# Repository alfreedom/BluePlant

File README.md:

# BluePlant
Dispositivo de sensado para plantas ornamentales y jardines

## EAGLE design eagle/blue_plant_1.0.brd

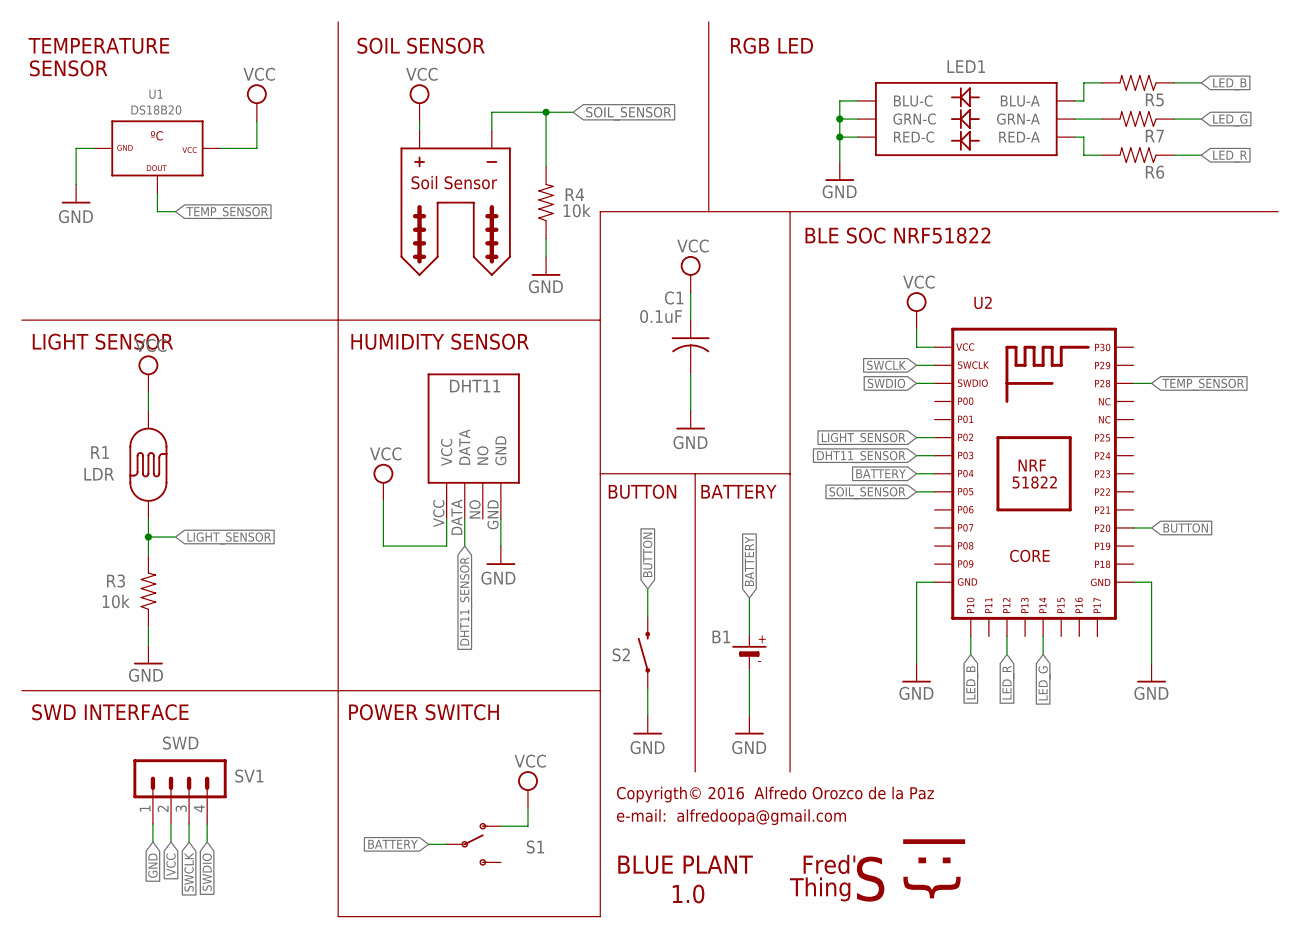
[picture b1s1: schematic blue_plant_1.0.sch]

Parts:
B1: BATTERYCR2032; CR2032
C1: 0.1uF; C025_050-025X075
LED1: RGB-5050; LED-TRICOLOR-5050
R1: LDR; PHOTOCELL-KIT
R2: SOIL-SENSOR; SOIL-SENSOR-1
R3, R4: 10k; AXIAL-0.3-KIT
R5, R6, R7: RESISTORKIT; AXIAL-0.3-KIT
S1: SWITCH-SPDT-SMD-A; SWITCH-SPST-SMD-A
S2: SWITCH-MOMENTARY-2SMD; TACTILE_SWITCH_SMD
SV1: SWD; MA04-1
U1: DS18B20; TO-92
U2: NRF51822-CORE-2; NRF51822-CORE2
U$1: DHT11

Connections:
BATTERY: B1.+, S1.2, U2.P18 (P04)
BUTTON: S2.3 (2), U2.P20
DHT11_SENSOR: U2.P17 (P03), U$1.DATA
GND: B1.-, C1.2, LED1.4 (BLU-C), LED1.5 (RED-C), LED1.6 (GRN-C), R3.P$1 (1), R4.P$1 (1), S2.1, SV1.1, U1.1 (GND), U2.P1 (GND1), U2.P12 (GND2), U$1.GND
LED_B: R5.P$1 (1), U2.P32 (P10)
LED_G: R7.P$1 (1), U2.P28 (P14)
LED_R: R6.P$1 (1), U2.P30 (P12)
LIGHT_SENSOR: R1.1, R3.P$2 (2), U2.P16 (P02)
unnamed: LED1.1 (GRN-A), R7.P$2 (2)
unnamed: LED1.3 (BLU-A), R5.P$2 (2)
unnamed: LED1.2 (RED-A), R6.P$2 (2)
SOIL_SENSOR: R2.P$1 (PG), R4.P$2 (2), U2.P35 (P05)
SWCLK: SV1.3, U2.P24 (SWDCLK)
SWDIO: SV1.4, U2.P23 (SWDIO)
TEMP_SENSOR: U1.2 (DOUT), U2.P9 (P28)
VCC: C1.1, R1.2, R2.P$2 (PS), S1.1 (O), SV1.2, U1.3 (VCC), U2.P11 (VCC), U$1.VCC

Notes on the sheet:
Copyrigth© 2016 Alfredo Orozco de la Paz
e-mail: alfredoopa@gmail.com
Fred'
{:|
BLUE PLANT
Thing
1.0
TEMPERATURE
SENSOR
SOIL SENSOR
RGB LED
BLE SOC NRF51822
POWER SWITCH
SWD INTERFACE
HUMIDITY SENSOR
LIGHT SENSOR
BUTTON
BATTERY

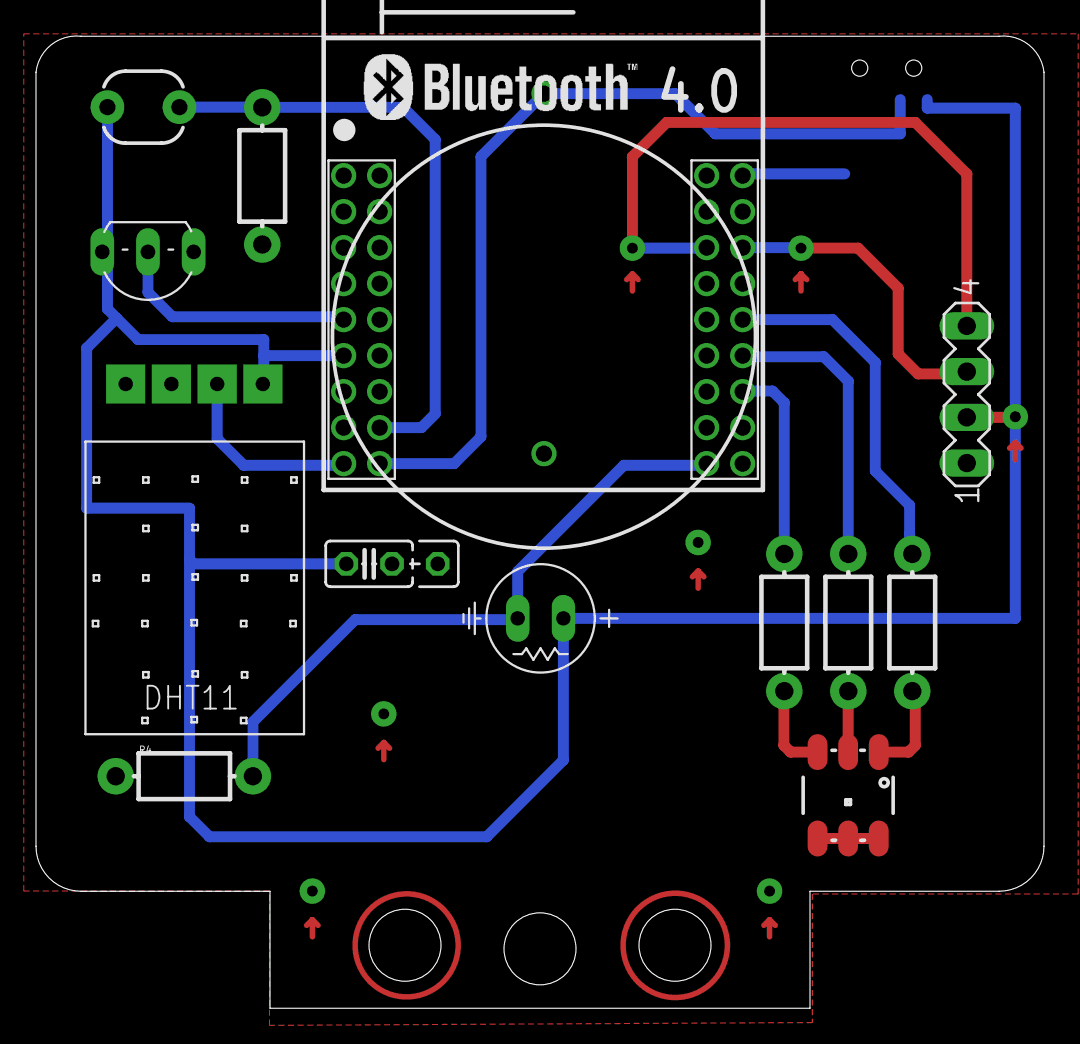
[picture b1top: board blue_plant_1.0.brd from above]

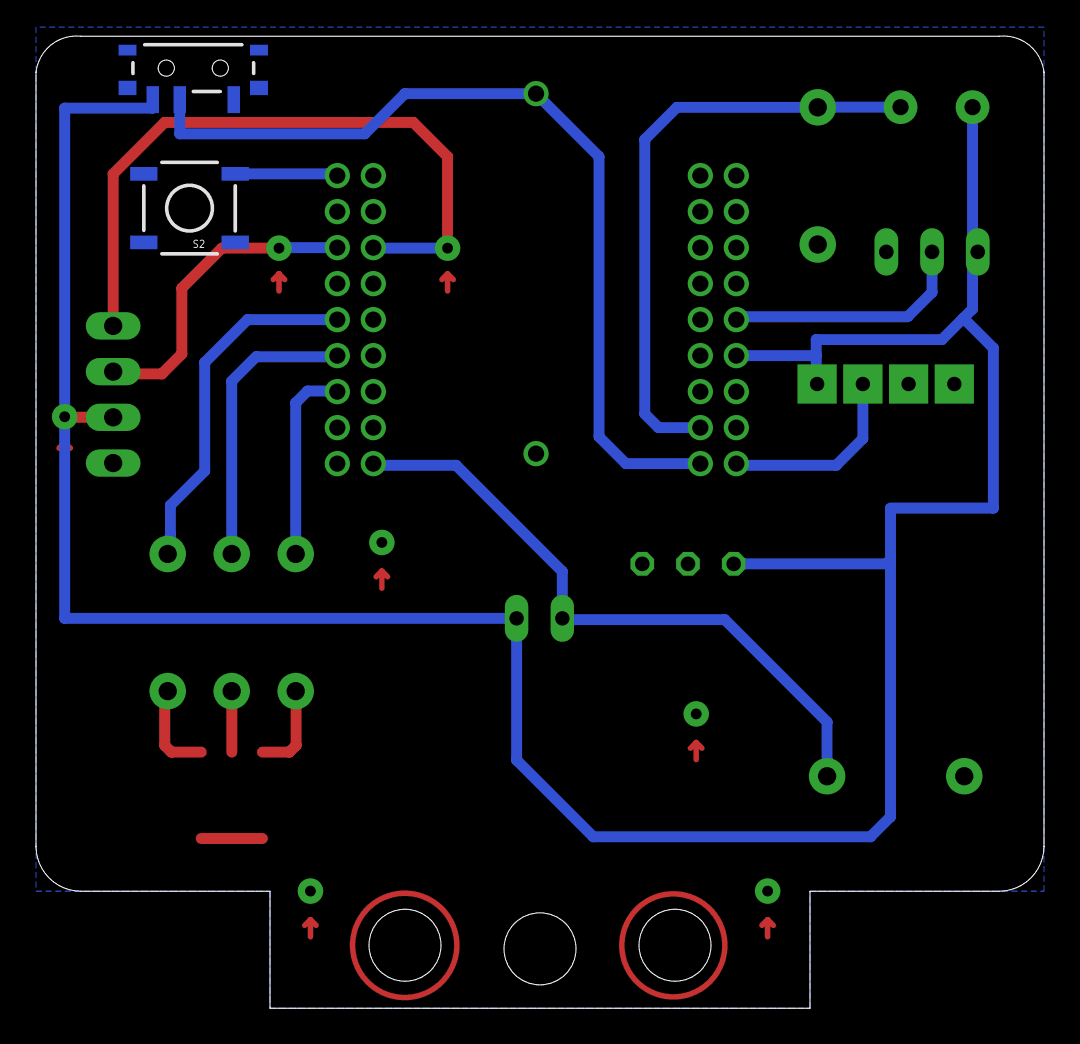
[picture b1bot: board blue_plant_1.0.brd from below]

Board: 2 copper layers, 56.0 x 54.0 mm, 16 parts (2 on the bottom side), 16 nets.

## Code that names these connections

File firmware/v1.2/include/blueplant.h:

 /***************************************************************************************
 *
 *     Copyrigth© 2016  Alfredo Orozco de la Paz 
 *     e-mail:  alfredoopa@gmail.com 
 *                
 *     Descripción
 *                
 *          Ĺibrería que define los componentes conectados a la tarjeta Blue Plant,
 *          es decir, a que pines del chip NRF51822 están conectados los sensores,
 *          leds y el push button.
 *          
 ***************************************************************************************
 *     Licencia:
 *
 *        Este programa es software libre; usted lo puede distribuir y/o modificar
 *        bajo los terminos   de la General Public License GNU, según es publicada
 *        en la  Free  Software  Foundation;  ya se la versión 2 de la Licencia, o
 *        (a su elección) una versión posterior.
 *
 *        Este  programa se  distribuye  con la  esperanza  de que sea  útil, pero
 *        SIN   NINGUNA   GARANTÍA,  incluso   sin   la   garantía   implícita  de
 *        COMERCIALIZACIÓN  o  IDONEIDAD PARA UN PROPÓSITO PARTICULAR. consulte la
 *        Licencia Pública General de GNU para más detalles.
 *
 *        Debería haber recibido una copia de  la  Licencia Pública General de GNU
 *        junto con este programa; si no, visite http://www.gnu.org/licenses.
 *      
 ***************************************************************************************/


/**
 * Todas las definiciones de estos pines se pueden cambiar acorde a la placa, es decir
 * se puede re-definir este archivo y agregar más conexiones según el diseño de la placa.
 * 
 * El chip NRF51822 puede redirecciónas las salidas de sus periféricos (UART,SPI,TWI.. etc)
 * a cualquier pin GPIO, esto da versatilidad y facilidad a la hora de realizar un diseño
 * con este chip.
 */

/**
* Librería de definiciones para la tarjeta Blue Plant
*/

#ifndef _BLUE_PLANT_H_
#define _BLUE_PLANT_H_


#define LED_R_PIN       22      // Led 2 de la tarjeta, pin GPIO del LED 2 (Activo en alto)
#define LED_G_PIN       21      // Led 3 de la tarjeta, pin GPIO del LED 3 (Activo en alto)
#define LED_B_PIN       20      // Led 4 de la tarjeta, pin GPIO del LED 4 (Activo en alto)

// El push button de la placa está conectado a tierra en un extremo y a un pin del NRF51822 en el otro,
// por lo que se debe configurar resistencias PULL-UP para el push button
#define BUTTON_PIN      16                      // Push button 1 (En la placa KEY1)    
#define BUTTON_PULL     NRF_GPIO_PIN_PULLUP     // Configuración de la resistencia para los botones (PULL-UP o PULL-DOWN), 

// Definiciones de pines para los sensores de la tarjeta.
#define DS18B20_SENSOR_PIN      28                      // (pin #28) Pin para el bus One Wire.
#define LIGHT_SENSOR_PIN        NRF_ADC_CONFIG_INPUT_2  // (pin #02) Pin para el sensor de luz (analógico).
#define DHT11_SENSOR_PIN        3                       // (pin #03) Pin para el sensor de temperatura y humedad DHT11.
#define SOIL_SENSOR_PIN         NRF_ADC_CONFIG_INPUT_6  // (pin #05) Pin para el sensor de humedad de la tierra (analógico).
//#define BATTERY_PIN             NRF_ADC_CONFIG_INPUT_5  // (pin #04) Pin para medir el voltaje de la batería (analógico).
#endif // _BLUE_PLANT_H_

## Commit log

2017-12-05 Added eagle files

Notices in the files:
parts and their libraries:
SparkFun-Sensors: Licensing: CC v3.0 Share-Alike You are welcome to use this library for commercial purposes.
microbuilder: This work is placed in the public domain, and may be freely used for commercial and non-commercial work with the following conditions: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
